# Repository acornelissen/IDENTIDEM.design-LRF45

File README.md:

This is a camera that's been a long time coming. As far as I know, there's nothing quite like it out there. 

**This is the Custom PCB version - it's a little more compact, but requires a custom PCB order. KiCAD and Gerber files are provided. There's no build guide specific to this version, but I'm going to assume if you're considering this version you'll be able to figure it out.**

**There's also a connector for a linear slide potentiometer on the PCB and an optional lens assembly STEP file that uses this instead of an optical sensor to measure lens extension, but I never took it further than that, so there's not code for this - and I never tested it in practice. It's there if you want to try it, though.** 

The LRF45 is a mostly 3D-printed camera with a LiDAR-powered digital rangefinder that is electronically coupled to a sensor that reads the lens extension. Which makes this a lens-coupled, hand-held large-format rangefinder. It also has a built-in light meter!

- It is designed for the Fujinon-W 105mm f5.6
- It is compatible with any Graflok film back, even the Lomograflok with some caveats
- The electronics are freely available, affordable, and easy to find
- The viewfinder optics and lens proper are the most expensive parts of this camera, and even those are relatively affordable and easy to procure
- The source code that powers the electronics and rangefinder (as well as light-meter) is open-source and can be found on Github
- There's a detailed build guide in PDF format below
- There's an OrcaSlicer file with all the hard work done for you, but if you want to slice it yourself, all the 3MFs are available as seperate files
- I also provide a STEP file with all the parts if you want to modify or remix the camera to use it with different lenses or formats

I really hope someone out there attempts to build this, and shoot with it. I want to see your makes, as well as your photos!
I have a few example photos on Instagram:

https://www.instagram.com/p/C1C5XITI7D1/
https://www.instagram.com/p/C1MwscKobC5/
https://www.instagram.com/p/C1XakoNo_7q/
https://www.instagram.com/p/C1zOQ6SIrhM/

The light leak in the first three posts has been fixed in the release version.

---
🍺 <strong><a href="https://paypal.me/albertcor">Buy me a beer</a></strong> if you'd like to say thank you.

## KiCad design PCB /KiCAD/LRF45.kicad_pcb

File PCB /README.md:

These are the Custom PCB files for the LRF45 PCB version. It's nothing special, just somewhere to neatly mount components and use JST connectors instead of having to solder wires directly to the Feather. It also adds a second push button for easier navigation of the UI. 

One thing you might be wondering is, why is there a connector for a potentiometer? Currently unused, but the idea was to open up the possibillity of using a slide-potentiometer instead of optical sensor to measure lens extension. The STEP files include designs for just this, but I never tested it in practice. So it's up to you whether you want to try it or not. The other option is to use it as an additional input, seeing as it's just a connection to one of the ADC pins.

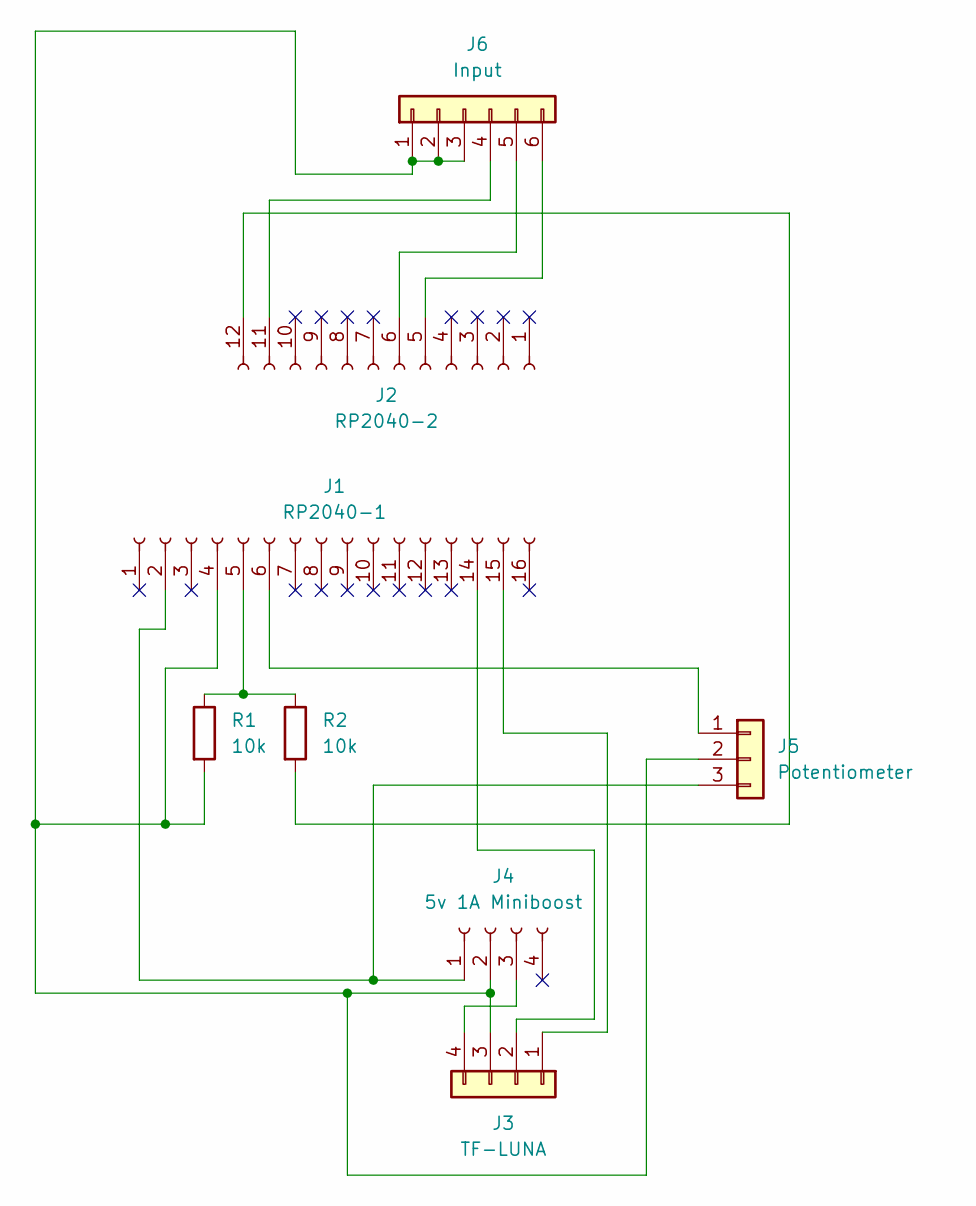
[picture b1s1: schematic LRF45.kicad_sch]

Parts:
J1: RP2040-1; PinHeader_1x16_P2.54mm_Vertical
J2: RP2040-2; PinHeader_1x12_P2.54mm_Vertical
J3: TF-LUNA; JST_XH_B4B-XH-A_1x04_P2.50mm_Vertical
J4: 5v 1A Miniboost; PinHeader_1x04_P2.54mm_Vertical
J5: Potentiometer; JST_XH_B3B-XH-A_1x03_P2.50mm_Vertical
J6: Input; JST_XH_B6B-XH-AM_1x06_P2.50mm_Vertical
R1, R2: 10k; R_1206_3216Metric

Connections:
unnamed: J1.2, J4.1, J5.3
unnamed: J1.4, J3.3, J4.2, J5.2, J6.1, J6.2, J6.3, R1.2
unnamed: J1.5, R1.1, R2.1
unnamed: J1.6, J5.1
unnamed: J1.14, J3.2
unnamed: J1.15, J3.1
unnamed: J2.5, J6.6
unnamed: J2.6, J6.5
unnamed: J2.11, J6.4
unnamed: J2.12, R2.2
unnamed: J3.4, J4.3

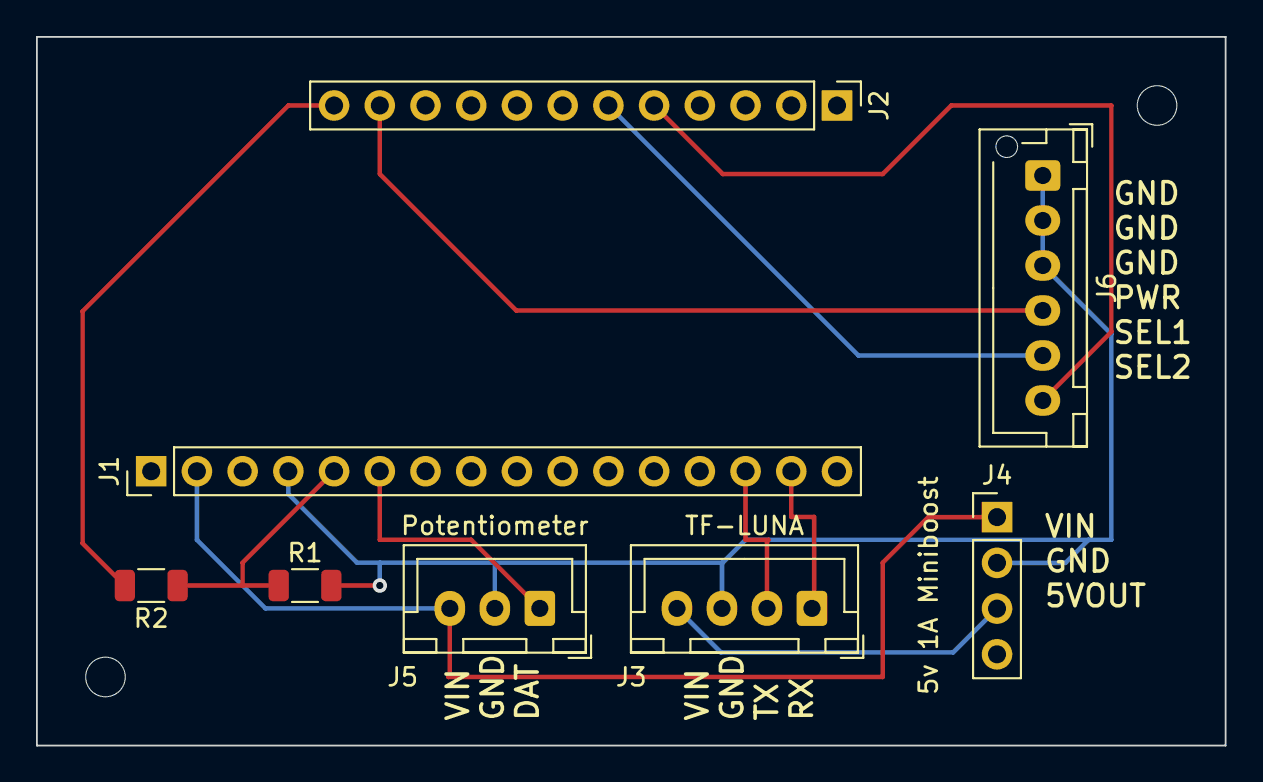
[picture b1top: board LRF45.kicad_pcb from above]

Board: 2 copper layers, 66.0 x 39.4 mm, 8 parts (0 on the bottom side), 11 nets.

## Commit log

2024-01-12 Use proper method to load config from JSON, make calculate_radius function more readable, move missed magic numbers to constants.
2024-01-12 Add link back to build guide and 3D print files.
2024-01-13 Improve the radius calculation and fix a bug where I was using storing the sensor value to the state, when I should have been saving the calculated focus distance,
2024-01-14 Fix a typo in the code and readme
2024-01-18 Update min and max focus distance for 105mm after better calibration. Tweak a few UI things.
2024-04-28 Add all CAD files and build guide.
2024-04-28 Add PCB version files.
2026-04-19 Replace build guide file with proper build guide PDF.
